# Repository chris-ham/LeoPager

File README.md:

# LeoPager
Project that enables a web page interface running on a Raspberry Pi to send 433MHz pager messages using a LeoStick.<br />
The restaurant pagers that have been tested with this design are from AliExpress https://www.aliexpress.com/item/Guest-Coaster-Pager-System-for-order-taking-one-set-CTP320/32816821424.html?spm=a2g0s.9042311.0.0.RaPpa7<br />

The above pager 'sets' each have a unique (as far as I know) identifier ie 1010100000111011 this is followed by the ID of the individual unit LSB first so pager 1 is 100000000 pager 2 is 010000000 etc<br />

The LeoStick https://www.freetronics.com.au/products/leostick#.WfGg4miCwUE receives messages via its USB interface and transmits the pager message out of a software serial port.<br />

Messages can also be received when the LeoStick is put into the correct mode.<br />

Message format is all human readable ASCII ie ?61010100000111011010000000\n<br />
+first byte is the number of times to send the message data - ie 9 sends message 9 times, ? sends it 15 times<br />
+Second byte is the delay between messages<br />
+rest of message contains the actual message to send. This message is an ASCII representation of binary ie 011011001...<br />
So ?61010100000111011010000000\n sends 1010100000111011010000000 15 times with a delay of 6 to the 2nd pager in bank 1010100000111011<br />

Sending the serial message 'GetCode' to the LeoStick will result in the 433MHz codes received by the receiver being echoed out the LeoStick's USB serial port. This will show the received message as 1010100000111011010000000 or such repeated several times. There will be the odd short message received however that is to be expected. These received messages  can be used to work out the bank number of the pager.<br />
  
Sending the serial message 'SendCode' will result in the 433MHz code reception being turned off<br />
The default is to not echo received codes<br />

The pagers can also be put into a 'learn code' mode if needed. See the scanned pager user manual in this hub for info on how to put them into learn mode.

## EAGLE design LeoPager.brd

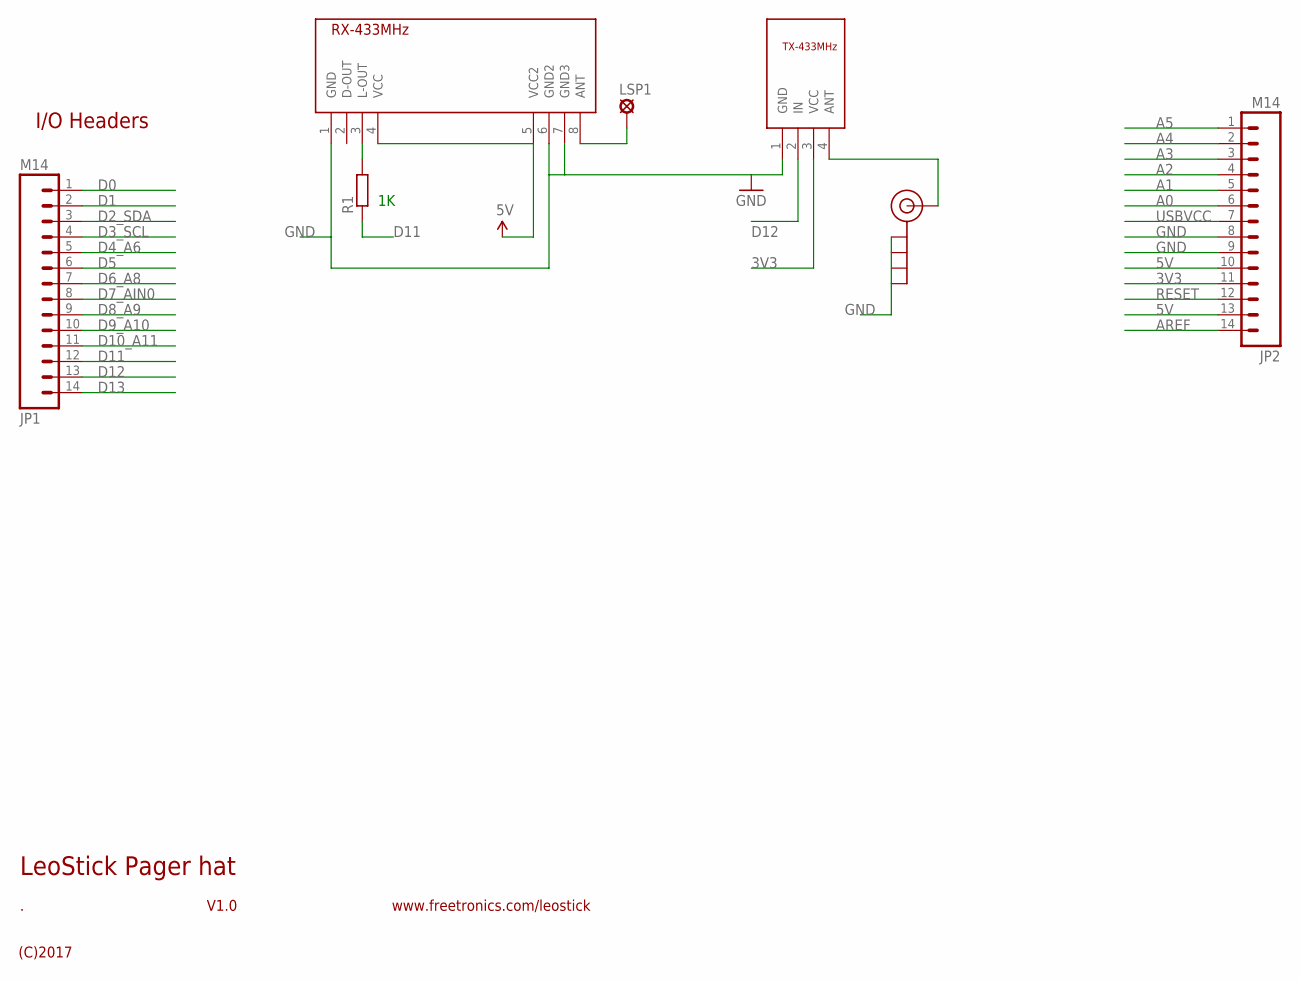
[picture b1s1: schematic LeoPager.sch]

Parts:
J$1: SMA_EDGE; SMA-EDGE
JP1, JP2: M14; 1X14
LSP1: LSP10
R1: R-EU_0204/7; 0204/7
RF-MODULE1: RX-433MHZ
RF-MODULE2: TX-433MHZ

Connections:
3V3: JP2.11, RF-MODULE2.3 (VCC)
5V: JP2.10, JP2.13, RF-MODULE1.4 (VCC), RF-MODULE1.5 (VCC2)
A0: JP2.6
A1: JP2.5
A2: JP2.4
A3: JP2.3
A4: JP2.2
A5: JP2.1
AREF: JP2.14
D0: JP1.1
D1: JP1.2
D2_SDA: JP1.3
D3_SCL: JP1.4
D4_A6: JP1.5
D5: JP1.6
D6_A8: JP1.7
D7_AIN0: JP1.8
D8_A9: JP1.9
D9_A10: JP1.10
D10_A11: JP1.11
D11: JP1.12, R1.1
D12: JP1.13, RF-MODULE2.2 (IN)
D13: JP1.14
GND: J$1.GND@0 (GND), J$1.GND@1 (GND), J$1.GND@2 (GND), J$1.GND@3 (GND), JP2.8, JP2.9, RF-MODULE1.1 (GND), RF-MODULE1.6 (GND2), RF-MODULE1.7 (GND3), RF-MODULE2.1 (GND)
unnamed: R1.2, RF-MODULE1.3 (L-OUT)
unnamed: J$1.SIG (SIGNAL), RF-MODULE2.4 (ANT)
unnamed: LSP1.MP, RF-MODULE1.8 (ANT)
RESET: JP2.12
USBVCC: JP2.7

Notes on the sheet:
I/O Headers
LeoStick Pager hat
V1.0
(C)2017
www.freetronics.com/leostick

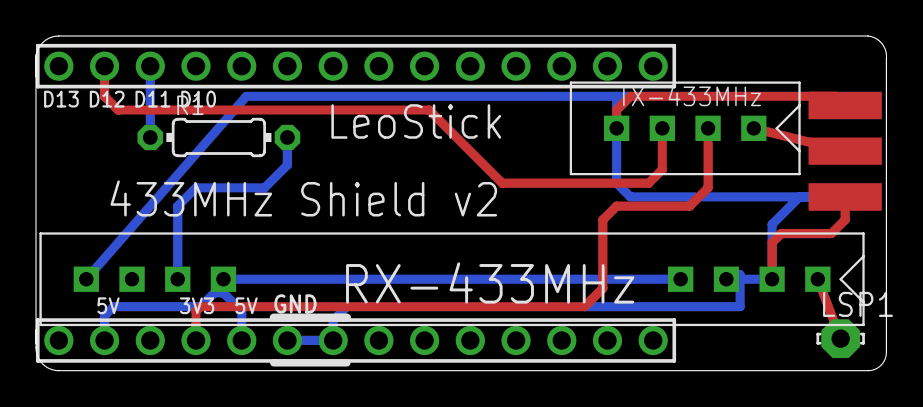
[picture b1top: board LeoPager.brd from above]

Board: 2 copper layers, 47.3 x 18.6 mm, 7 parts (0 on the bottom side), 8 nets.

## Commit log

2017-10-18 Gerber files for Leostick hat v2
    Full set of Gerber files that are used to create the 433MHz hat for the Arduino Leostick hat
2017-10-18 Autodesk Eagle files for LeoPager
    The PCB was designed using Autodesk's Eagle CAD software.
2017-10-18 Arduino software
    Application that runs on the Arduino Leostick that transmits the 433MHz pager message
2017-10-26 Add files via upload
    Added data sheets for tested 433MHZ RX and TX units and SMA connector
2017-10-26 Update README.md
    Updated description
2017-10-26 Update README.md
    Added pager ref
2017-10-26 Update README.md
    Added more description of messages etc
2017-10-26 Add files via upload
    Added user manual for Wireless Calling System as it is supplied with the pagers
